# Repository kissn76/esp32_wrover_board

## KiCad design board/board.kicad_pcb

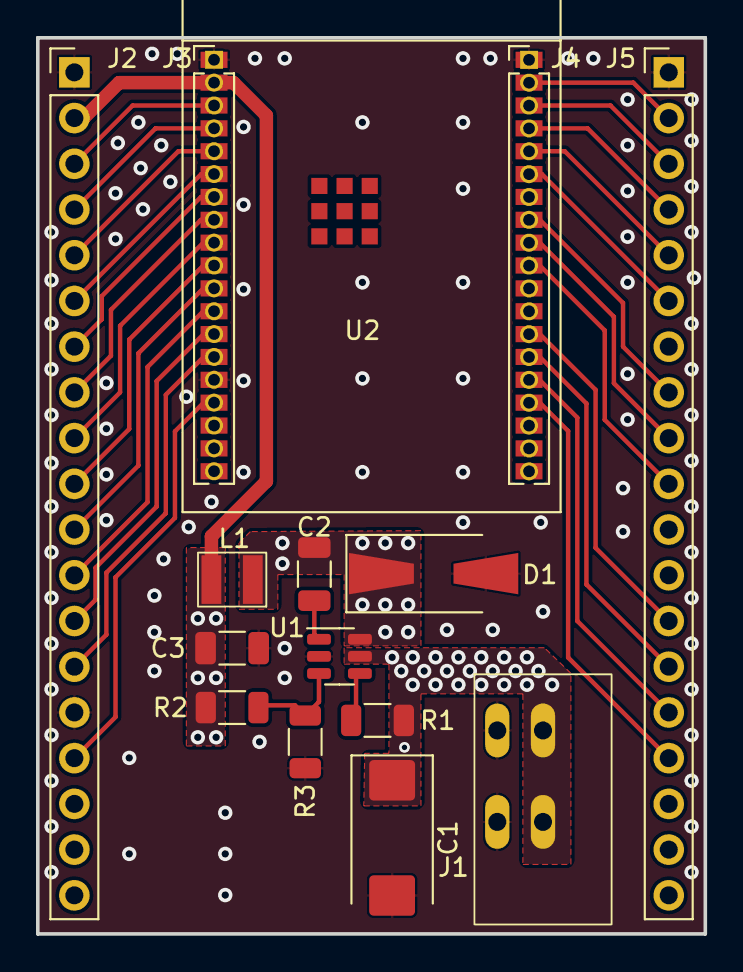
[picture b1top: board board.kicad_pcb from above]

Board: 2 copper layers, 37.1 x 49.8 mm, 15 parts (0 on the bottom side), 32 nets.

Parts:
C1: 4.7uF; CP_EIA-7343-31_Kemet-D_Pad2.25x2.55mm_HandSolder
C2: 10nF; C_1206_3216Metric
C3: 10uF; C_1206_3216Metric
D1: Schottky SMA-SMB; D_SMA-SMB_Universal_Handsoldering
J1: 5-26V; Ninigi AC141R-02P-2.54
J2, J5: Conn_01x19; PinHeader_1x19_P2.54mm_Vertical
J3, J4: Conn_01x19; PinHeader_1x19_P1.27mm_Vertical
L1: 2.2uH; Shielded_3.0_3.0
R1: 100k - 600k; R_1206_3216Metric
R2: 49.9kΩ; R_1206_3216Metric
R3: 15.8kΩ; R_1206_3216Metric
U1: AOZ1280CI; SOT-23-6
U2: ESP32-WROVER-E; ESP32-WROVER-IE

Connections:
3.3: C3.1, J2.2, J3.2, L1.2, R2.1, U2.2 (3V3)
/VIN: C1.1, J1.2, R1.1, U1.5 (VIN)
/VOUT: C2.2, D1.1 (K), L1.1, U1.6 (LX)
GND: C1.2, C3.2, D1.2 (A), J1.1, J2.1, J2.15, J3.1, J3.15, J4.1, J5.1, R3.2, U1.2 (GND), U2.1 (GND), U2.15 (GND), U2.38 (GND)
unnamed: J2.3, J3.3, U2.3 (EN)
unnamed: J2.4, J3.4, U2.4 (SENSOR_VP)
unnamed: J2.5, J3.5, U2.5 (SENSOR_VN)
unnamed: J2.6, J3.6, U2.6 (IO34)
unnamed: J2.7, J3.7, U2.7 (IO35)
unnamed: J2.8, J3.8, U2.8 (IO32)
unnamed: J2.9, J3.9, U2.9 (IO33)
unnamed: J2.10, J3.10, U2.10 (IO25)
unnamed: J2.11, J3.11, U2.11 (IO26)
unnamed: J2.12, J3.12, U2.12 (IO27)
unnamed: J2.13, J3.13, U2.13 (IO14)
unnamed: J2.14, J3.14, U2.14 (IO12)
unnamed: J2.16, J3.16, U2.16 (IO13)
unnamed: J4.2, J5.2, U2.37 (IO23)
unnamed: J4.3, J5.3, U2.36 (IO22)
unnamed: J4.4, J5.4, U2.35 (TXD0)
unnamed: J4.5, J5.5, U2.34 (RXD0)
unnamed: J4.6, J5.6, U2.33 (IO21)
unnamed: J4.8, J5.8, U2.31 (IO19)
unnamed: J4.9, J5.9, U2.30 (IO18)
unnamed: J4.10, J5.10, U2.29 (IO5)
unnamed: J4.13, J5.13, U2.26 (IO4)
unnamed: J4.14, J5.14, U2.25 (IO0)
unnamed: J4.15, J5.15, U2.24 (IO2)
unnamed: J4.16, J5.16, U2.23 (IO15)
unnamed: C2.1, U1.1 (BST)
unnamed: R1.2, U1.4 (EN)
unnamed: R2.2, R3.1, U1.3 (FB)
